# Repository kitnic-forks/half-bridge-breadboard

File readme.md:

# Purpose #

This is a KiCad project that documents a simple half-bridge circuit, complete with driver.  The
circuit includes room for two TO-220 MOSFETs, two snubber circuits.  It has two logic-level inputs 
which will turn on the upper and lower MOSFETs.

# Details of Operation #

## Power Supply ##

If 10V < V<sub>BATT</sub> < 20V, then the jumper at P2 may be connected so that the
[FAN7842MX](https://www.fairchildsemi.com/datasheets/FA/FAN7842.pdf) is properly supplied.

If V<sub>BATT</sub> < 10V or V<sub>BATT</sub> > 20V, then the user must supply a voltage
between 10V and 20V to the circuit using pin 1 of P1.

## PWM Frequency ##

The circuit is intended to operate as a complete half-bridge using Pulse Width Modulation (PWM) on
the high side AND the low side.  When the upper MOSFET is being operated, it must be operated
synchronously with the lower MOSFET in order to charge the bootstrap capacitor.  The minimum recommended
PWM frequency is 10kHz.

When only the lower MOSFET is being operated, then the upper MOSFET input may be held low while the
lower MOSFET is operated at any frequency desired, including DC.

## Specifications ##

The circuit is intended to operate at a maximum voltage of ~35V and 5A, but these are limitations of
the components and not of the circuit board.  The board - with the proper capacitors and MOSFETs -
should be able to operate as high as 200V at a current of up to 20A.

## Connections ##

### Breadboard ###

If the breatboard power rails are between 10V and 20V and the expected current is under 1A, then P1,
P2, and P3 can be populated on the underside of the board and simply plugged into the breadboard.

When the voltage is outside of the 10V to 20V range, then only pins 1, 2, and 3 of P2 should be
populated and plugged into the breadboard.  The 10V-20V should be supplied to the board through
pin 1 of P1.

### Screw Terminals ###

If P2 is not populated, then power may be supplied through the screw terminals on P4.

# Why Do This? #

I know that there are lots of these sorts of circuits available, but I am continually finding myself
re-drawing this schematic for different circuits.  By placing all of the components for the half-bridge
on one circuit, I have a flexible and extendable starting point for a host of circuits.  Applications
include:

 * DC-DC conversion
 * DC motor drives
 * BLDC motor drives
 
I had a look around and didn't see anything quite like it on Tindie nor a couple of other sites that
I frequent.  World, here ya go.

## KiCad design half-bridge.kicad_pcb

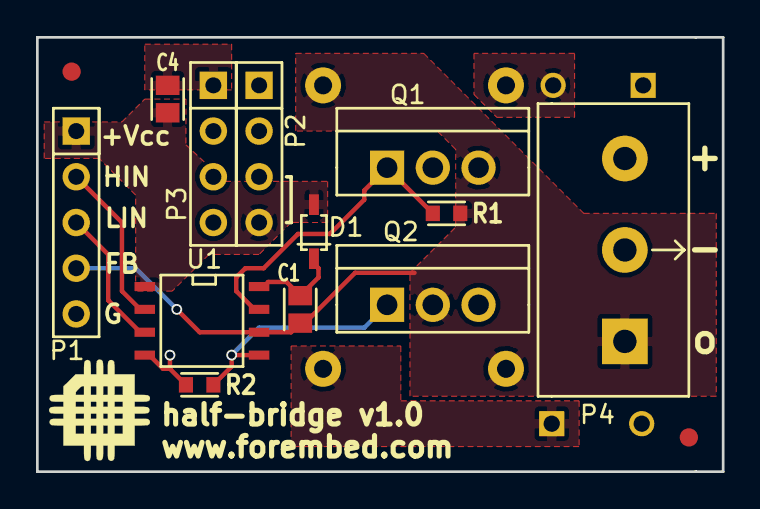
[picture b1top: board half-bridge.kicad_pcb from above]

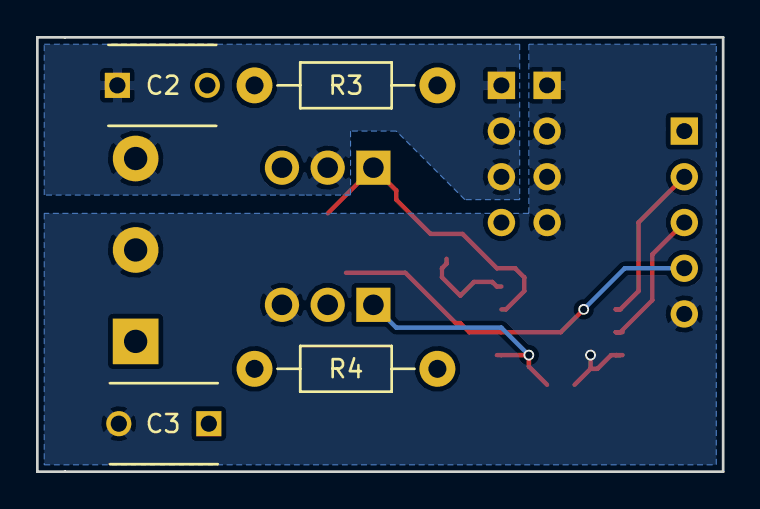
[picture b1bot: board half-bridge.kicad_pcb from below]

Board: 2 copper layers, 38.1 x 24.1 mm, 18 parts (4 on the bottom side), 11 nets.

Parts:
C1, C4: 1uF 50V; SM_0805
C2, C3: CSNUB; C_Disc_D6_P5
D1: D; SOD-323
FID1, FID1#2: fiducial
P1: CONN_01X05; CON_1x5_0.1in
P2, P3: CONN_01X04; CON_1x4_0.1in
P4: CONN_01X03; CONN_1x3_OSTTC032162
Q1, Q2: Q_NMOS_GDS; TO-220-VERTICAL
R1, R2: 1k; SM_0603
R3, R4: RSNUB; Resistor_Horizontal_RM10mm
U1: MOSFET_DRIVER_FAN7842MX; SOIC-8-N

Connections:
+12V: C4.1, D1.2, P1.1, P2.4, U1.1
+BATT: C2.1, P2.1, P2.2, P2.3, P4.3, Q1.2
/Vout: C1.2, P1.4, P4.1, Q1.3, Q2.2, R1.2, R3.2, R4.1, U1.6
GND: C3.2, C4.2, P1.5, P3.1, P3.2, P3.3, P3.4, P4.2, Q2.3, R2.2, U1.4
unnamed: C1.1, D1.1, U1.8
unnamed: C2.2, R3.1
unnamed: C3.1, R4.2
unnamed: P1.2, U1.2
unnamed: P1.3, U1.3
unnamed: Q1.1, R1.1, U1.7
unnamed: Q2.1, R2.1, U1.5

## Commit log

2016-07-14 Initial schematic and layout for a half-bridge circuit
2016-07-14 Added notes to schematic
2016-07-14 Added PDF version of the schematic
2016-07-14 Updated print settings of the project file
2016-07-15 Added output sense circuit
2016-07-15 Added revised schematic
2016-07-15 Added readme
